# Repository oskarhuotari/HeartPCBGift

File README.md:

# A gift for my GF

The PCB:
A heart shaped board that has 30 leds around the outer perimeter. The MCU used is the ATMEGA32U4 and the leds are controlled using charlieplexing. The PCB has an USB-C receptacle which in addition to powering the board enables programming. 

The stand:
I also designed a stand which allows the PCB to be mounted with M3 bolts.

The code:
It registers button presses and changes between led modes. The modes are all leds on, a sweep, random led on and all leds off.

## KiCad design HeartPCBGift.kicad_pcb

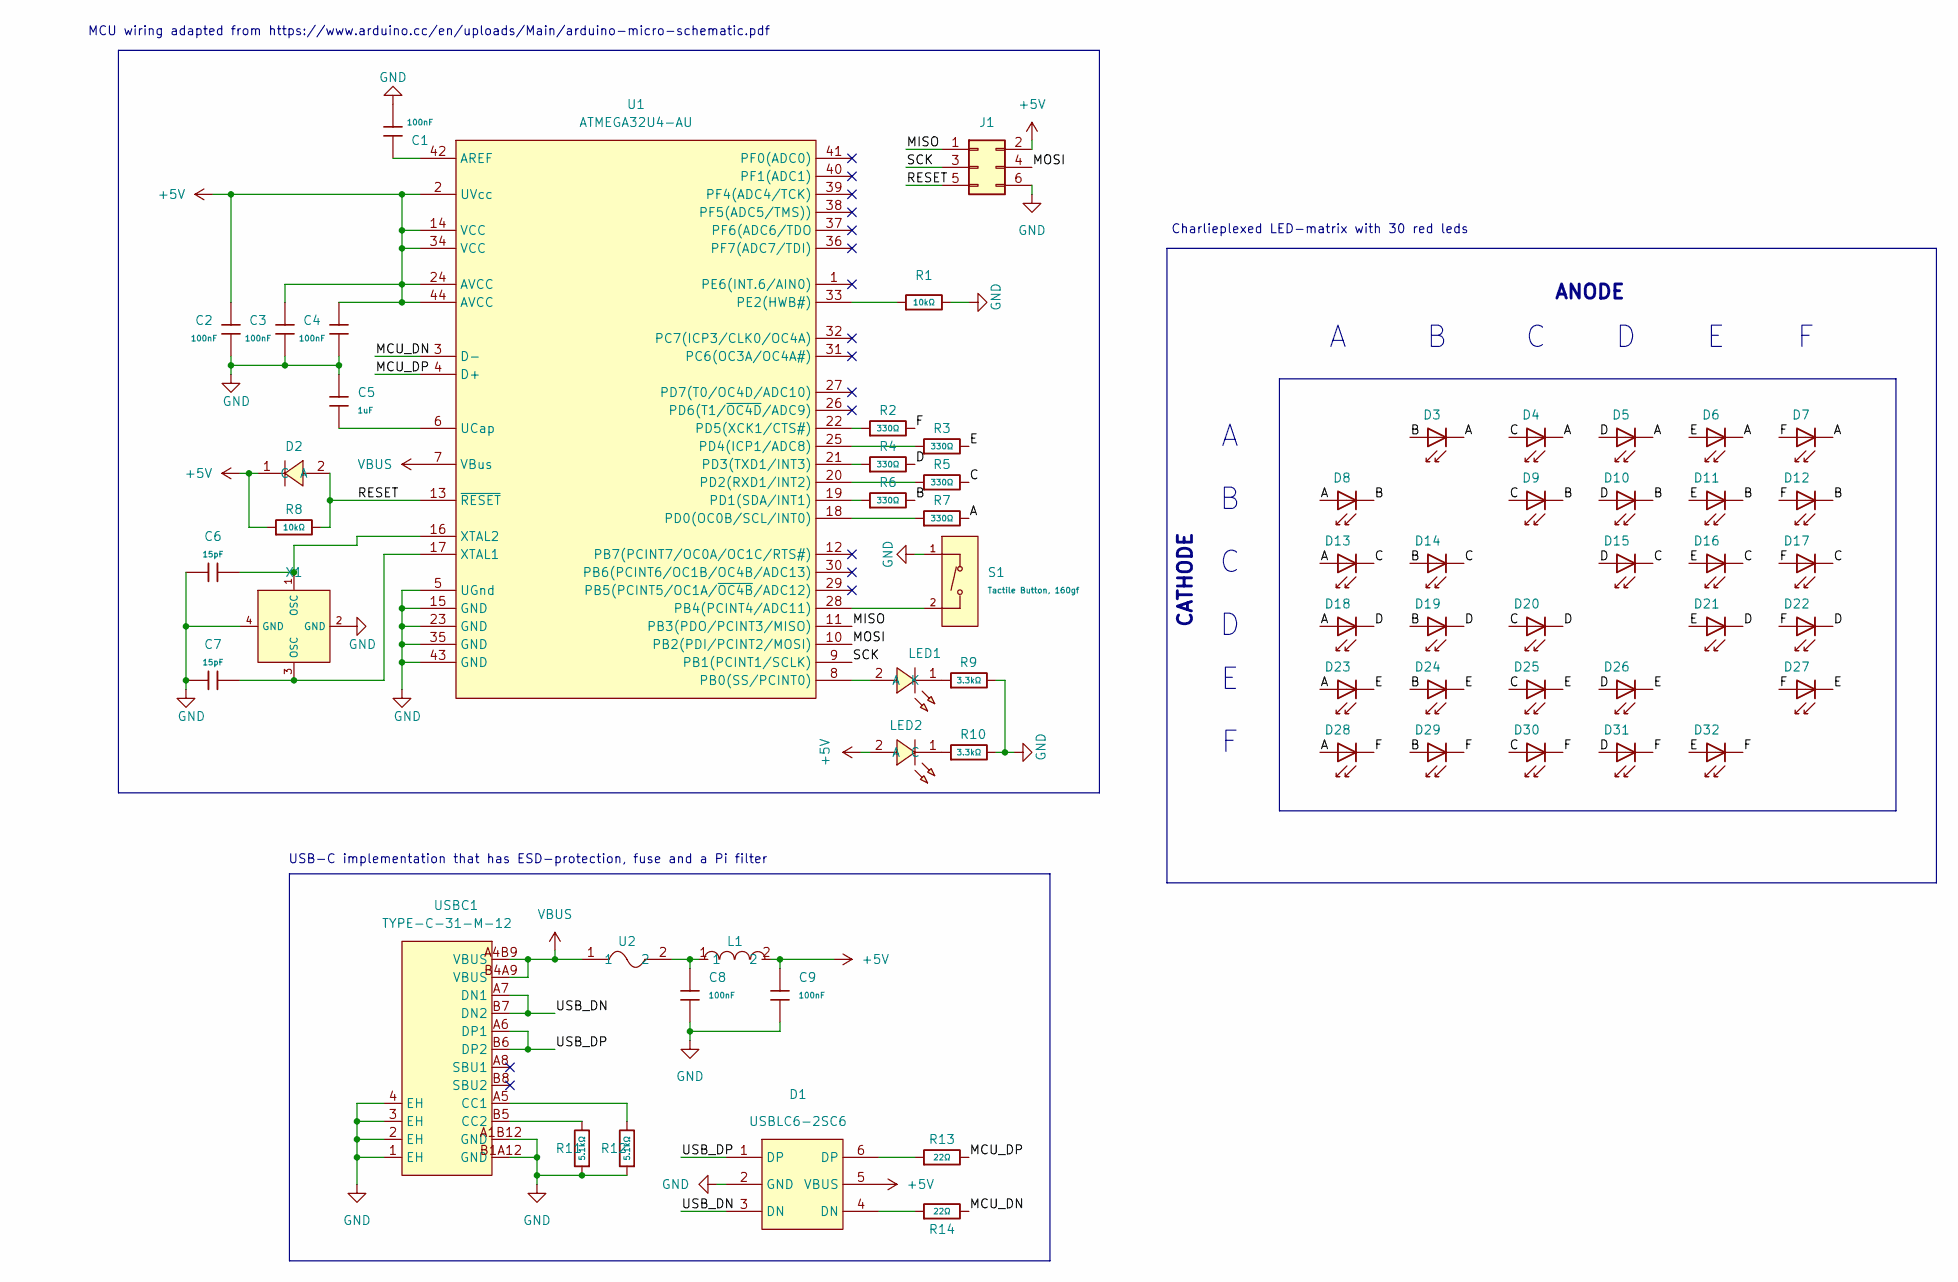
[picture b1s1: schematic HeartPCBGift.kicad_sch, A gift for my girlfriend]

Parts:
C1, C2, C3, C4, C8, C9: 100nF; C_0603; Voltage Rated 50V; Tolerance ±10%; Part CC0603KRX7R9BB104; LCSC C14663
C5: 1uF; C_0603; Voltage Rated 50V; Tolerance ±10%; Part CL10A105KB8NNNC; LCSC C15849
C6, C7: 15pF; C_0603; Voltage Rated 50V; Tolerance ±5%; Part CL10C150JB8NNNC; LCSC C1644
D1: USBLC6-2SC6; SOT-23-6_L2.9-W1.6-P0.95-LS2.8-BL; MPN USBLC6-2SC6; LCSC Part C7519
D2: 1N4448W_C5190208; SOD-123_L2.7-W1.6-LS3.7-RD; MPN 1N4448W; LCSC Part C5190208
D3, D4, D5, D6, D7, D8, D9, D10, D11, D12, D13, D14, D15, D16, D17, D18, D19, D20, D21, D22, D23, D24, D25, D26, D27, D28, D29, D30, D31, D32: Red; D_0805; Forward Voltage (VF) 1.6V~2.6V; Part NCD0805R1; LCSC C84256
J1: Conn_02x03_Odd_Even; PinHeader_2x03_P2.54mm_Vertical
L1: MPZ1608D101BTA00; L0603; MPN MPZ1608D101BTA00; LCSC Part C87554
LED1: XL-1608UBC-04; LED0603-RD_BLUE; MPN XL-1608UBC-04; LCSC Part C965807
LED2: F.0603.00025/P2-0603G1TS2-06T-002; LED0603-RD_GREEN; MPN F.0603.00025/P2-0603G1TS2-06T-002; LCSC Part C7496818
R1, R8: 10kΩ; R_0603; Overload Voltage (Max) 75V; Tolerance ±1%; Part 0603WAF1002T5E; LCSC C25804
R2, R3, R4, R5, R6, R7: 330Ω; R_0603; Overload Voltage (Max) 75V; Tolerance ±1%; Part 0603WAF3300T5E; LCSC C23138
R9, R10: 3.3kΩ; R_0603; Overload Voltage (Max) 75V; Tolerance ±1%; Part 0603WAF3301T5E; LCSC C22978
R11, R12: 5.1kΩ; R_0603; Overload Voltage (Max) 75V; Tolerance ±1%; Part 0603WAF5101T5E; LCSC C23186
R13, R14: 22Ω; R_0603; Overload Voltage (Max) 75V; Tolerance ±1%; Part 0603WAF220JT5E; LCSC C23345
S1: Tactile Button, 160gf; SW_TS-1088-AR02016; Voltage Rating (Dc) 12V; Part TS-1088-AR02016; LCSC C720477
U1: ATMEGA32U4-AU; QFP-44_L10.0-W10.0-P0.80-LS13.2-BL; MPN ATMEGA32U4-AU; LCSC Part C44854
U2: MF-MSMF050-2; F1812; MPN MF-MSMF050-2; LCSC Part C17313
USBC1: TYPE-C-31-M-12; USB-C_SMD-TYPE-C-31-M-12_1; MPN TYPE-C-31-M-12; LCSC Part C165948
X1: X322516MLB4SI; OSC-SMD_4P-L3.2-W2.5-BL; Frequency Tolerance ±10ppm; Part X322516MLB4SI; LCSC C13738

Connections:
+5V: C2.2, C3.2, C4.2, C9.1, D1.5 (VBUS), D2.1 (C), J1.2, L1.2, LED2.2 (A), R8.1, U1.2 (UVcc), U1.14 (VCC), U1.24 (AVCC), U1.34 (VCC), U1.44 (AVCC)
/A: D3.1, D4.1, D5.1, D6.1, D7.1, D8.2, D13.2, D18.2, D23.2, D28.2, R7.2
/B: D3.2, D8.1, D9.1, D10.1, D11.1, D12.1, D14.2, D19.2, D24.2, D29.2, R6.2
/C: D4.2, D9.2, D13.1, D14.1, D15.1, D16.1, D17.1, D20.2, D25.2, D30.2, R5.2
/D: D5.2, D10.2, D15.2, D18.1, D19.1, D20.1, D21.1, D22.1, D26.2, D31.2, R4.2
/E: D6.2, D11.2, D16.2, D21.2, D23.1, D24.1, D25.1, D26.1, D27.1, D32.2, R3.2
/F: D7.2, D12.2, D17.2, D22.2, D27.2, D28.1, D29.1, D30.1, D31.1, D32.1, R2.2
/MCU_DN: R14.2, U1.3 (D-)
/MCU_DP: R13.2, U1.4 (D+)
/MISO: J1.1, U1.11 (PB3(PDO/PCINT3/MISO))
/MOSI: J1.4, U1.10 (PB2(PDI/PCINT2/MOSI))
/RESET: D2.2 (A), J1.5, R8.2, U1.13 (~RESET)
/SCK: J1.3, U1.9 (PB1(PCINT1/SCLK))
/USB_DN: D1.3 (DN), USBC1.A7 (DN1), USBC1.B7 (DN2)
/USB_DP: D1.1 (DP), USBC1.A6 (DP1), USBC1.B6 (DP2)
GND: C1.1, C2.1, C3.1, C4.1, C5.1, C6.1, C7.1, C8.2, C9.2, D1.2 (GND), J1.6, R1.2, R9.2, R10.2, R11.1, R12.1, S1.1 (A), U1.5 (UGnd), U1.15 (GND), U1.23 (GND), U1.35 (GND), U1.43 (GND), USBC1.1 (EH), USBC1.2 (EH), USBC1.3 (EH), USBC1.4 (EH), USBC1.A1B12 (GND), USBC1.B1A12 (GND), X1.2 (GND), X1.4 (GND)
unnamed: C8.1, L1.1, U2.2
unnamed: D1.4 (DN), R14.1
unnamed: D1.6 (DP), R13.1
unnamed: LED1.2 (A), U1.8 (PB0(SS/PCINT0))
unnamed: LED1.1 (K), R9.1
unnamed: LED2.1 (C), R10.1
unnamed: S1.2 (B), U1.28 (PB4(PCINT4/ADC11))
unnamed: C1.2, U1.42 (AREF)
unnamed: R7.1, U1.18 (PD0(OC0B/SCL/INT0))
unnamed: R6.1, U1.19 (PD1(SDA/INT1))
unnamed: R5.1, U1.20 (PD2(RXD1/INT2))
unnamed: R4.1, U1.21 (PD3(TXD1/INT3))
unnamed: R3.1, U1.25 (PD4(ICP1/ADC8))
unnamed: R2.1, U1.22 (PD5(XCK1/CTS#))
unnamed: R1.1, U1.33 (PE2(HWB#))
unnamed: C5.2, U1.6 (UCap)
unnamed: C7.2, U1.17 (XTAL1), X1.3 (OSC)
unnamed: C6.2, U1.16 (XTAL2), X1.1 (OSC)
unnamed: R12.2, USBC1.A5 (CC1)
unnamed: R11.2, USBC1.B5 (CC2)
VBUS: U1.7 (VBus), U2.1, USBC1.A4B9 (VBUS), USBC1.B4A9 (VBUS)

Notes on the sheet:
Charlieplexed LED-matrix with 30 red leds
USB-C implementation that has ESD-protection, fuse and a Pi filter
ANODE
MCU wiring adapted from https://www.arduino.cc/en/uploads/Main/arduino-micro-schematic.pdf
CATHODE

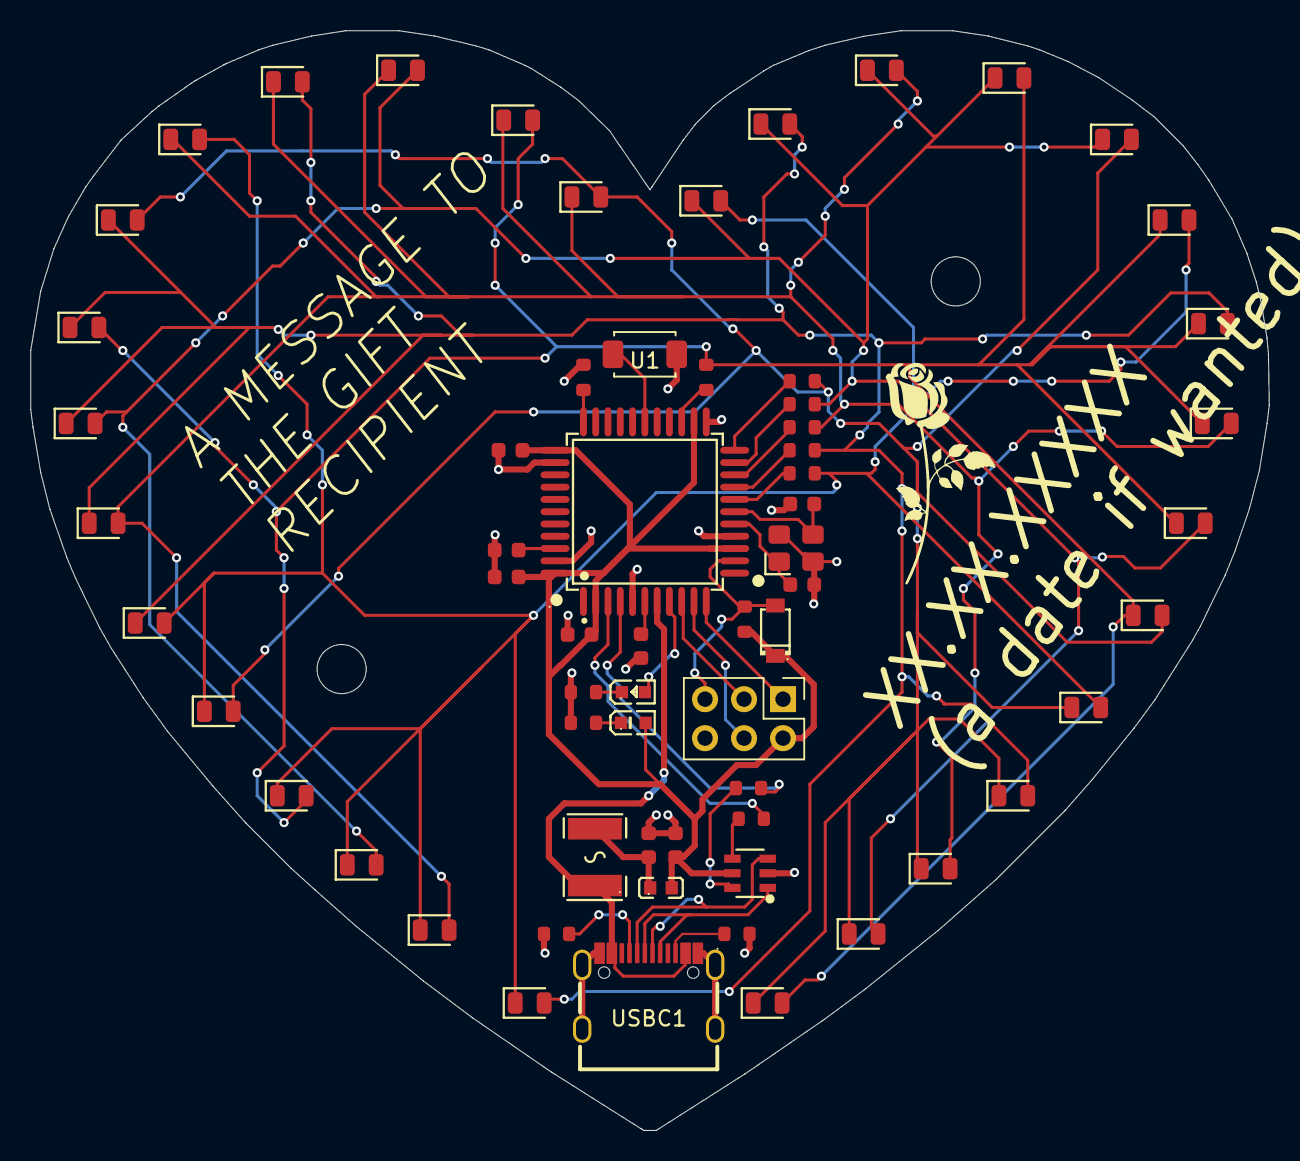
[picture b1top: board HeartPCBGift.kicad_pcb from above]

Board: 2 copper layers, 80.7 x 71.6 mm, 64 parts (0 on the bottom side), 37 nets.
